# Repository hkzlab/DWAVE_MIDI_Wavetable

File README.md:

# DWAVE: Dream Wavetable module

## Introduction

The DWAVE is a small General MIDI Synth based on the SAM2695 chip. It can be plugged on the wavetable header of your sound card.

### Disclaimer

I take NO responsibility for what happens if you decide to build and use this card. Your computer might crash, catch fire or be destroyed in other nasty ways.
You're encourauged to take what you deem fit from this, and use it in your projects!

## Bill of Materials

| Component         | Qty | Type / Value        | Mouser code           |
| ----------------- | --- | ------------------- | --------------------- |
| C1                | 2   | 1uF / 0805          | [710-885012207022](https://www.mouser.it/ProductDetail/710-885012207022) |
| C2                | 1   | 10nF / 0805         | [710-885382207006](https://www.mouser.it/ProductDetail/710-885382207006) |
| C3,C7             | 2   | 4.7uF / 0805        | [187-CL21A475KPFNNNG](https://www.mouser.it/ProductDetail/187-CL21A475KPFNNNG) |
| C4,C5             | 2   | 22pF / 0805         | [710-885012007053](https://www.mouser.it/ProductDetail/710-885012007053) |
| C6,C8,C9,C10,C15,C17,C21 | 7   | 100nF / 0805        | [710-885012207072](https://www.mouser.it/ProductDetail/710-885012207072) |
| C14,C16,C18       | 3   | 10uF / 0805         | [187-CL21A106KPFNNNG](https://www.mouser.it/ProductDetail/187-CL21A106KPFNNNG) |
| C19,C20           | 2   | 100uF / 1206        | [81-GRM31CR61A107ME5L](https://www.mouser.it/ProductDetail/81-GRM31CR61A107ME5L) |
| L1                | 1 (or 2)  | Inductor 742792093  | [710-742792093](https://www.mouser.it/ProductDetail/710-742792093) |
| R1                | 1 (or 0)  | 0 ohm or same as L1 | [71-CRCW08050000Z0EAC](https://www.mouser.it/ProductDetail/71-CRCW08050000Z0EAC) |
| R3,R4             | 2   | 47k / 0805          | [652-CR0805FX-4702ELF](https://www.mouser.it/ProductDetail/652-CR0805FX-4702ELF) |
| F1                | 1   | SMD Fuse            | [652-SF-1206HI050M-2](https://www.mouser.it/ProductDetail/652-SF-1206HI050M-2) |
| Y1                | 1   | 12Mhz / HC49        | [449-LFXTAL035293REEL](https://www.mouser.it/ProductDetail/449-LFXTAL035293REEL) |
| U1                | 1   | LP2085-3.3          | [926-LP2985IM5X33NOPB](https://www.mouser.it/ProductDetail/926-LP2985IM5X33NOPB) |
| U2                | 1   | SAM2695             | |
| U3                | 1   | 74HC4050            | [771-74HC4050PW-Q100J](https://www.mouser.it/ProductDetail/771-74HC4050PW-Q100J) |
| J1                | 1   | 2x13 2.54mm socket  | [200-SSQ11301GD](https://www.mouser.it/ProductDetail/Samtec/SSQ-113-01-G-D), but any snappable 2.54mm socket is fine |

## Credits

Thanks to [Sergey Kiselev](https://github.com/skiselev) for his symbol/footprint library!

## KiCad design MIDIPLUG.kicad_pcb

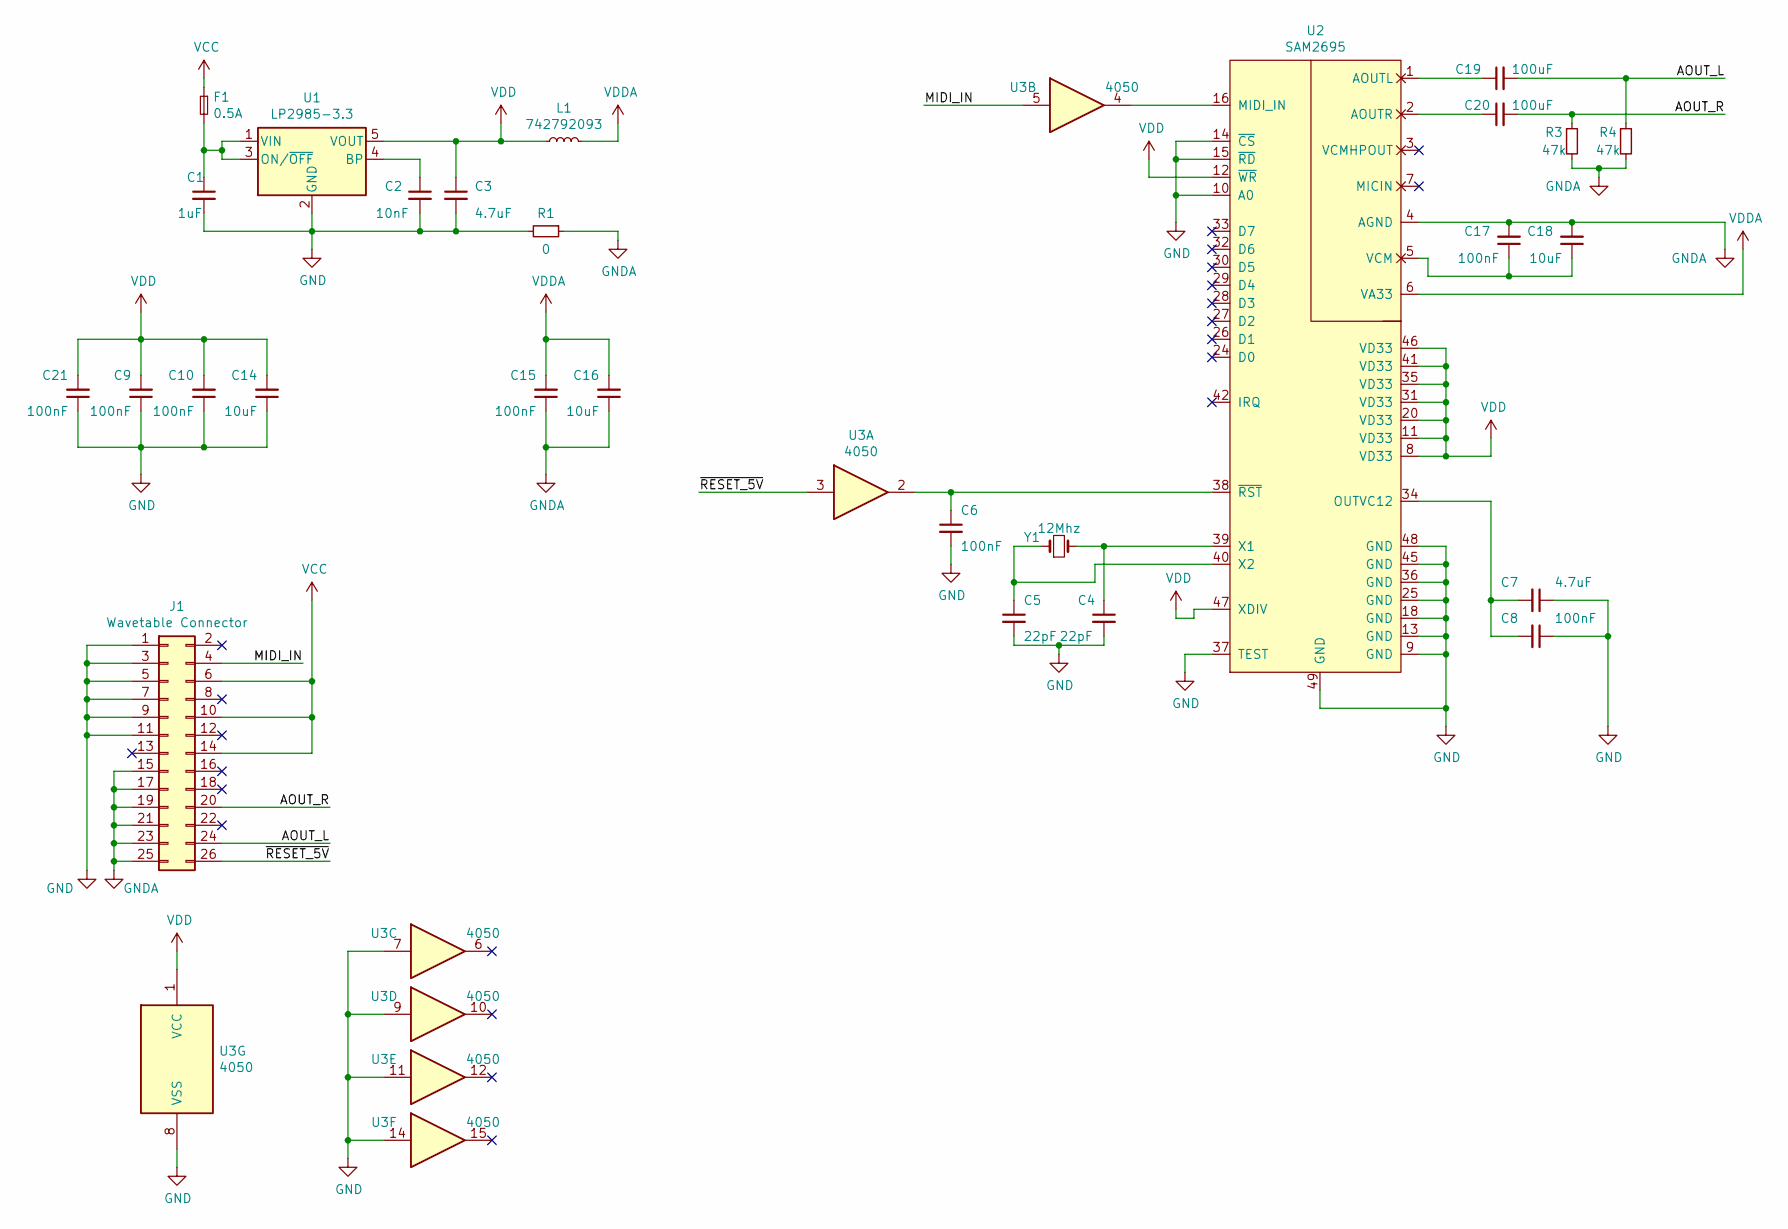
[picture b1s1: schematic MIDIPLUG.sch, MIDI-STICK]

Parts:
C1: 1uF; C_0805_2012Metric_Pad1.18x1.45mm_HandSolder
C2: 10nF; C_0805_2012Metric_Pad1.18x1.45mm_HandSolder
C3, C7: 4.7uF; C_0805_2012Metric_Pad1.18x1.45mm_HandSolder
C4, C5: 22pF; C_0805_2012Metric_Pad1.18x1.45mm_HandSolder
C6, C8, C9, C10, C15, C17, C21: 100nF; C_0805_2012Metric_Pad1.18x1.45mm_HandSolder
C14, C16, C18: 10uF; C_0805_2012Metric_Pad1.18x1.45mm_HandSolder
C19, C20: 100uF; C_1206_3216Metric_Pad1.33x1.80mm_HandSolder
F1: 0.5A; Fuse_1206_3216Metric_Pad1.42x1.75mm_HandSolder
J1: Wavetable Connector; PinSocket_2x13_P2.54mm_Vertical
L1: 742792093; L_0805_2012Metric_Pad1.15x1.40mm_HandSolder
R1: 0; R_0805_2012Metric_Pad1.20x1.40mm_HandSolder
R3, R4: 47k; R_0805_2012Metric_Pad1.20x1.40mm_HandSolder
U1: LP2985-3.3; SOT-23-5
U2: SAM2695; QFN-48-1EP_6x6mm_P0.4mm_EP4.66x4.66mm_BackHoles
U3: 4050; TSSOP-16_4.4x5mm_P0.65mm
Y1: 12Mhz; Crystal_SMD_HC49-SD

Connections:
/AOUT_L: C19.2, J1.24, R4.1
/AOUT_R: C20.2, J1.20, R3.1
/MIDI_IN: J1.4, U3.5
/~RESET_5V: J1.26, U3.3
GND: C1.2, C2.2, C3.2, C4.2, C5.2, C6.2, C7.1, C8.1, C9.1, C10.1, C14.1, C21.1, J1.1, J1.3, J1.5, J1.7, J1.9, J1.11, R1.2, U1.2 (GND), U2.9 (GND), U2.10 (A0), U2.13 (GND), U2.14 (~CS), U2.15 (~RD), U2.18 (GND), U2.25 (GND), U2.36 (GND), U2.37 (TEST), U2.45 (GND), U2.48 (GND), U2.49 (GND), U3.7, U3.8 (VSS), U3.9, U3.11, U3.14
GNDA: C15.1, C16.1, C17.2, C18.2, J1.15, J1.17, J1.19, J1.21, J1.23, J1.25, R1.1, R3.2, R4.2, U2.4 (AGND)
unnamed: C1.1, F1.2, U1.1 (VIN), U1.3 (ON/~OFF~)
unnamed: C2.1, U1.4 (BP)
unnamed: C4.1, U2.39 (X1), Y1.2
unnamed: C5.1, U2.40 (X2), Y1.1
unnamed: C6.1, U2.38 (~RST), U3.2
unnamed: C7.2, C8.2, U2.34 (OUTVC12)
unnamed: C17.1, C18.1, U2.5 (VCM)
unnamed: C19.1, U2.1 (AOUTL)
unnamed: C20.1, U2.2 (AOUTR)
unnamed: U2.16 (MIDI_IN), U3.4
VCC: F1.1, J1.6, J1.10, J1.14
VDD: C3.1, C9.2, C10.2, C14.2, C21.2, L1.1, U1.5 (VOUT), U2.8 (VD33), U2.11 (VD33), U2.12 (~WR), U2.20 (VD33), U2.31 (VD33), U2.35 (VD33), U2.41 (VD33), U2.46 (VD33), U2.47 (XDIV), U3.1 (VCC)
VDDA: C15.2, C16.2, L1.2, U2.6 (VA33)

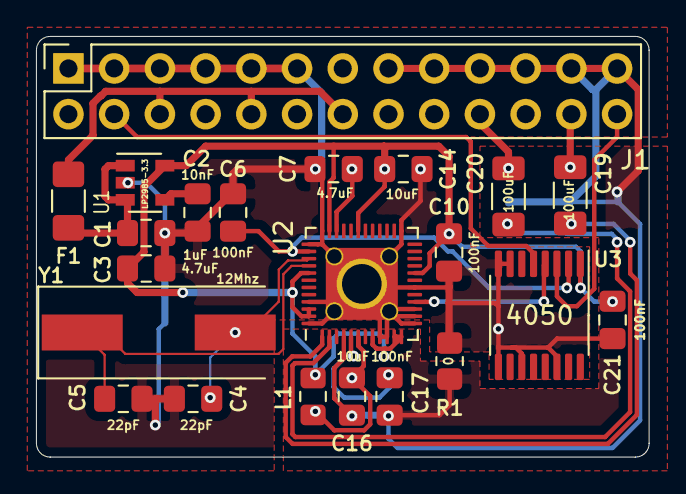
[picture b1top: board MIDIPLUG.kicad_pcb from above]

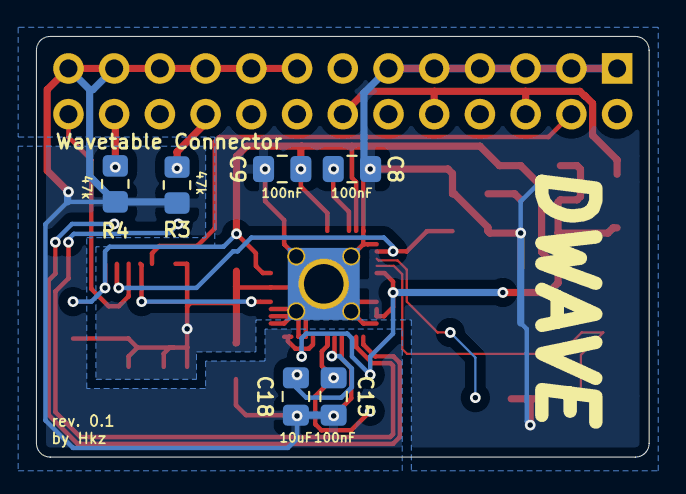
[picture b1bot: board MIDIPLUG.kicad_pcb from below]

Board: 2 copper layers, 34.0 x 23.4 mm, 28 parts (6 on the bottom side), 19 nets.

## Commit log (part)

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2021-05-29 Add empty library for SAM2695
2021-05-29 Add symbol for SAM2695
2021-05-30 Add basic circuit for midi plug
2021-05-30 Add joystick plug
2021-05-30 Begin placing components
2021-05-30 First version of the PCB
2021-05-30 Some more connections and tweaks of copper zones
2021-05-31 More silkscreen adjustments
2021-05-31 Tweak silkscreen
2021-05-31 Small changes to silkscreen
2021-06-11 Add traces to bottom layer for the heatsink
2021-06-11 Change the silkscreen a bit
2021-06-11 Change gnd plane
2021-06-16 Add SAM2695 datasheet
2021-06-16 Add hole on underside of SAM chip
2021-06-16 Generate gerbers for rev 0.1
2021-06-16 Changed footprint
2021-07-01 Rewrite the schematics to support waveblaster
2021-07-01 Begin reorganizing board
2021-07-01 Routed internal version
2021-07-01 Add bypass cap for 4050
2021-07-01 Moved around some components
2021-07-01 Fixed silkscreen
2021-07-01 Changed some things in silkscreen
2021-07-01 Add dimensions
2021-07-01 Connect GNDA
2021-07-01 Add rev 0.1 gerbers
2021-07-01 Add missing mask on backside and redo gerbers
2021-08-10 Renamed some filed
2021-08-10 Add pics and README
2021-11-09 Update KiCad URL
